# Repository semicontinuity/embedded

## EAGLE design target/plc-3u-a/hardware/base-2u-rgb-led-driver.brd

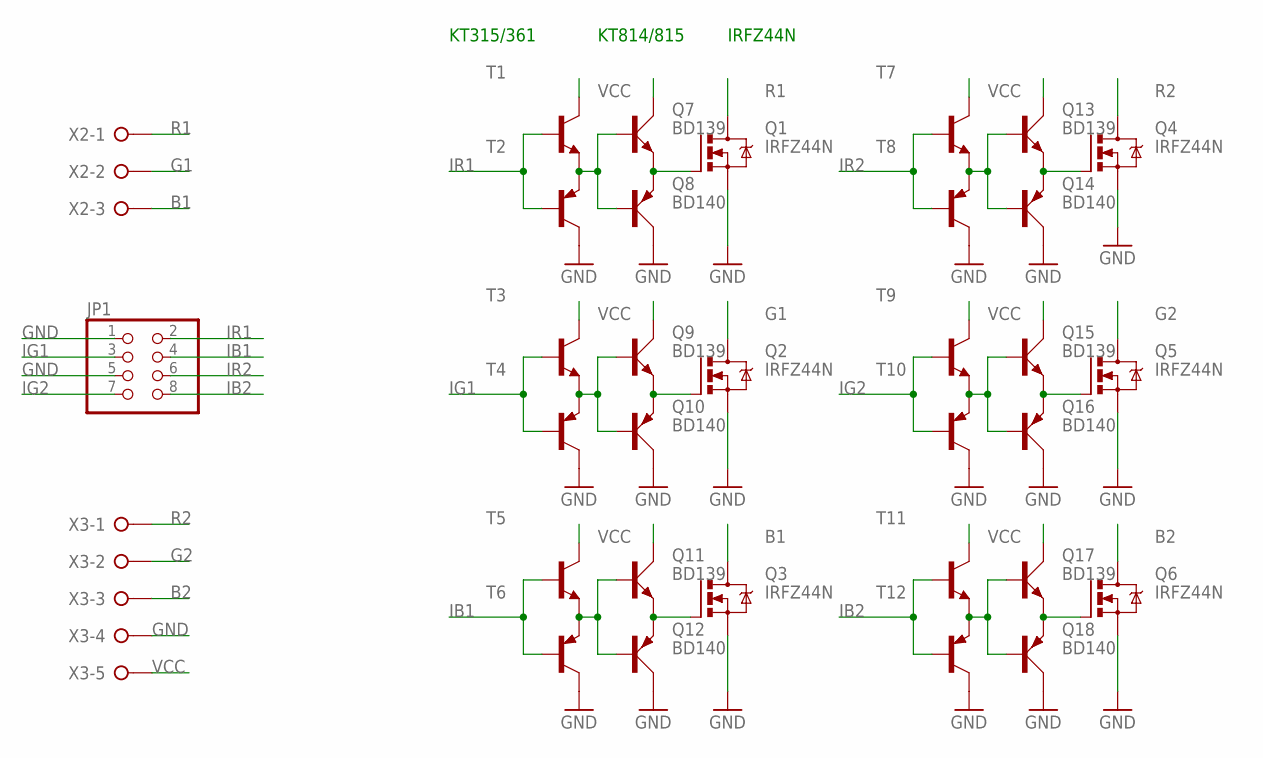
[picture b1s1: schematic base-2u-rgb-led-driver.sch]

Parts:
JP1: PINHD-2X4/90; 2X04/90
Q1, Q2, Q3, Q4, Q5, Q6: IRFZ44N; TO220BV
Q7, Q9, Q11, Q13, Q15, Q17: BD139; TO126AV
Q8, Q10, Q12, Q14, Q16, Q18: BD140; TO126AV
T1, T3, T5, T7, T9, T11: BC637-NPN-TO92-ECB; TO92-ECB
T2, T4, T6, T8, T10, T12: BC638-PNP-TO92-BCE; TO92-BCE
X2: W237-03P; W237-133
X3: W237-05P; W237-5P

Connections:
B1: Q3.D, X2.3
B2: Q6.D, X3.3
DB1: Q11.B, Q12.B, T5.E, T6.E
DB2: Q17.B, Q18.B, T11.E, T12.E
DG1: Q9.B, Q10.B, T3.E, T4.E
DG2: Q15.B, Q16.B, T9.E, T10.E
DR1: Q7.B, Q8.B, T1.E, T2.E
DR2: Q13.B, Q14.B, T7.E, T8.E
G1: Q2.D, X2.2
G2: Q5.D, X3.2
GND: JP1.1, JP1.5, Q1.S, Q2.S, Q3.S, Q4.S, Q5.S, Q6.S, Q8.C, Q10.C, Q12.C, Q14.C, Q16.C, Q18.C, T2.C, T4.C, T6.C, T8.C, T10.C, T12.C, X3.4
IB1: JP1.4, T5.B, T6.B
IB2: JP1.8, T11.B, T12.B
IG1: JP1.3, T3.B, T4.B
IG2: JP1.7, T9.B, T10.B
IR1: JP1.2, T1.B, T2.B
IR2: JP1.6, T7.B, T8.B
unnamed: Q1.G, Q7.E, Q8.E
unnamed: Q4.G, Q13.E, Q14.E
unnamed: Q2.G, Q9.E, Q10.E
unnamed: Q3.G, Q11.E, Q12.E
unnamed: Q5.G, Q15.E, Q16.E
unnamed: Q6.G, Q17.E, Q18.E
R1: Q1.D, X2.1
R2: Q4.D, X3.1
VCC: Q7.C, Q9.C, Q11.C, Q13.C, Q15.C, Q17.C, T1.C, T3.C, T5.C, T7.C, T9.C, T11.C, X3.5

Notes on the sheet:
IRFZ44N
KT315/361
KT814/815

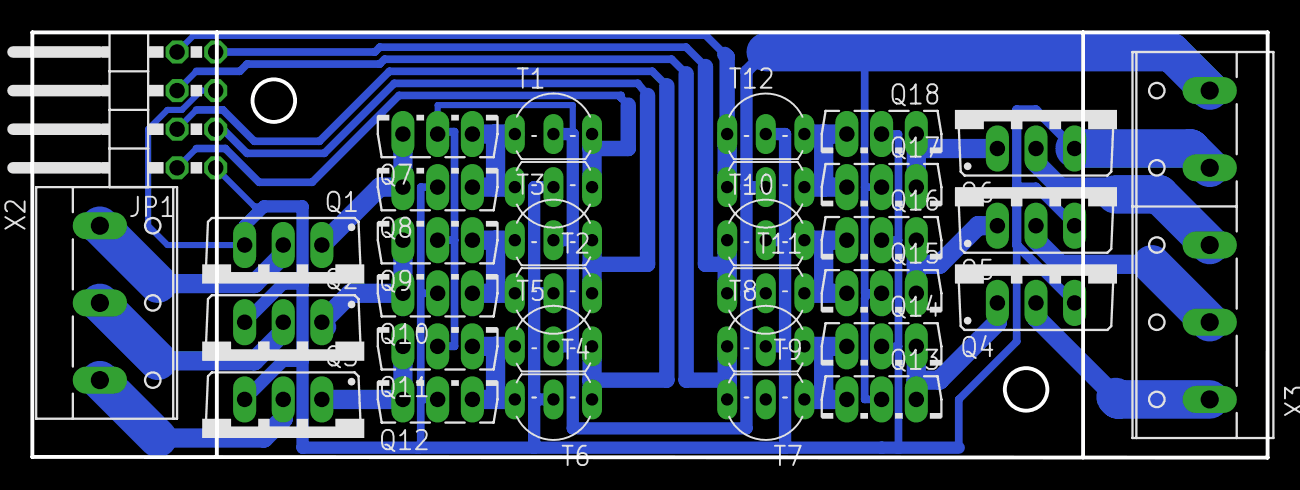
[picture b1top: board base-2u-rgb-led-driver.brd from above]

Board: 2 copper layers, 81.3 x 28.0 mm, 33 parts (0 on the bottom side), 26 nets.

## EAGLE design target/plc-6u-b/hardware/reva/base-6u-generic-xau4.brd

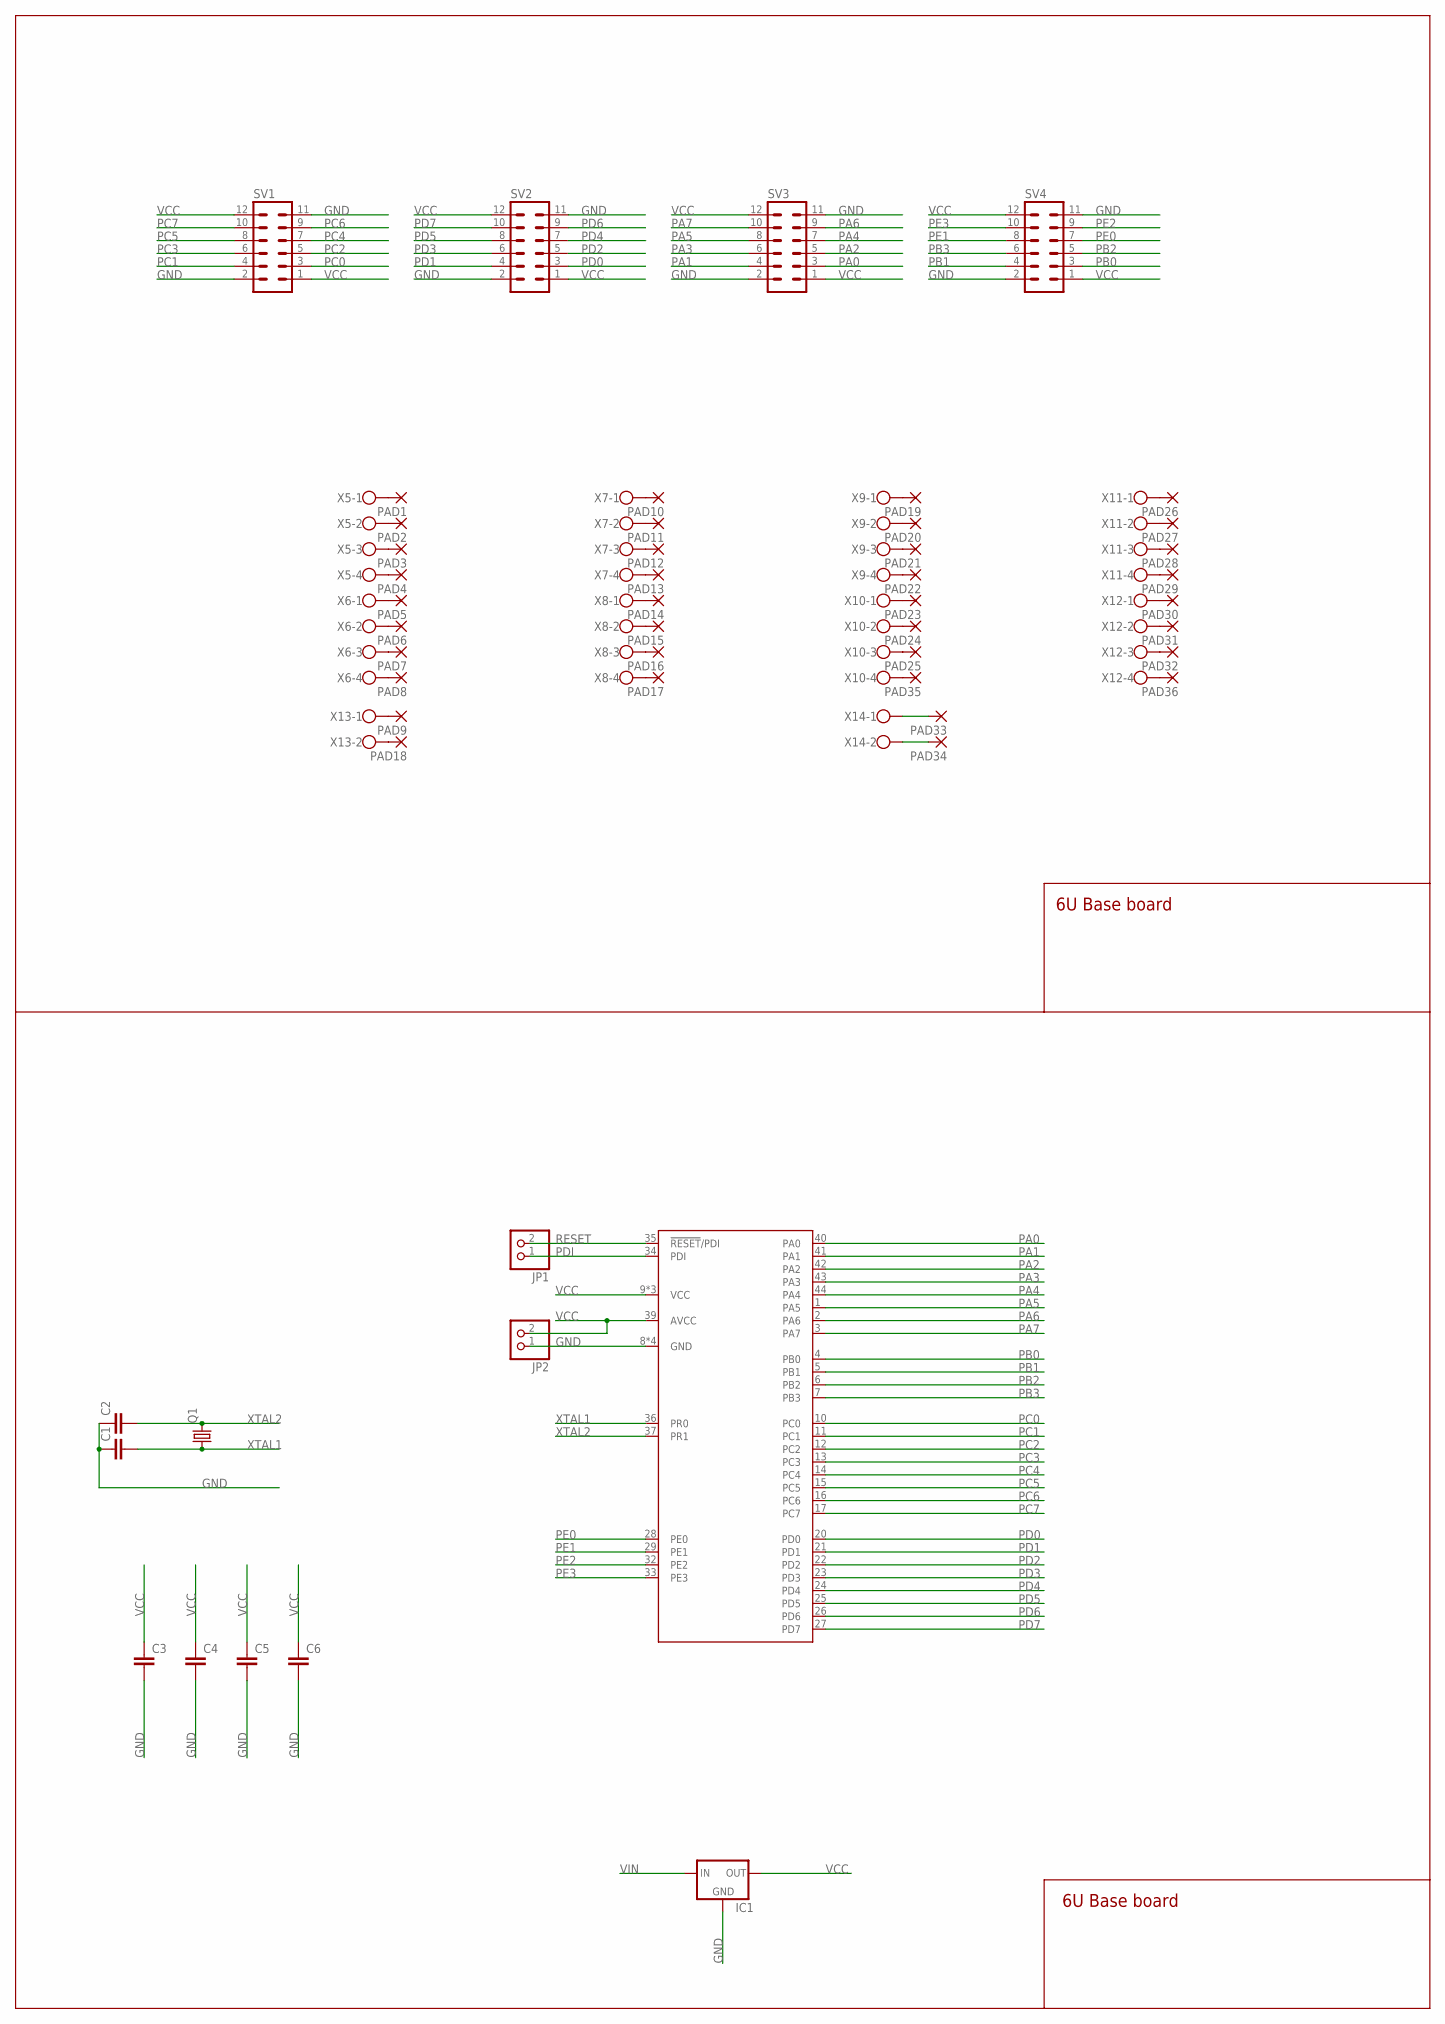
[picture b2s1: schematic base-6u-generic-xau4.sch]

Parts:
C1, C2: C-EUC0805; C0805
C3, C4, C5, C6: C-EUC0603; C0603
IC1: LM1117TO252; TO252
JP1, JP2: PINHD-1X2; 1X02
PAD1, PAD2, PAD3, PAD4, PAD5, PAD6, PAD7, PAD8, PAD9, PAD10, PAD11, PAD12, PAD13, PAD14, PAD15, PAD16, PAD17, PAD18, PAD19, PAD20, PAD21, PAD22, PAD23, PAD24, PAD25, PAD26, PAD27, PAD28, PAD29, PAD30, PAD31, PAD32, PAD33, PAD34, PAD35, PAD36: 2,54/0,8
Q1: CRYSTALHC49S; HC49/S
SV1, SV2, SV3, SV4: MA06-2
U1: ATXMEGA32A4U-AU; TQFP-44A-44
X5, X6, X7, X8, X9, X10, X11, X12: W237-4
X13, X14: W237-102

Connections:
GND: C1.1, C2.1, C3.2, C4.2, C5.2, C6.2, IC1.1 (GND), JP2.1, PAD33.1, SV1.2, SV1.11, SV2.2, SV2.11, SV3.2, SV3.11, SV4.2, SV4.11, U1.8 (GND), U1.18 (GND), U1.30 (GND), U1.38 (GND), X14.1
unnamed: PAD1.1, X5.1
unnamed: PAD2.1, X5.2
unnamed: PAD3.1, X5.3
unnamed: PAD4.1, X5.4
unnamed: PAD5.1, X6.1
unnamed: PAD6.1, X6.2
unnamed: PAD7.1, X6.3
unnamed: PAD8.1, X6.4
unnamed: PAD9.1, X13.1
unnamed: PAD10.1, X7.1
unnamed: PAD11.1, X7.2
unnamed: PAD12.1, X7.3
unnamed: PAD13.1, X7.4
unnamed: PAD14.1, X8.1
unnamed: PAD15.1, X8.2
unnamed: PAD16.1, X8.3
unnamed: PAD17.1, X8.4
unnamed: PAD18.1, X13.2
unnamed: PAD26.1, X11.1
unnamed: PAD27.1, X11.2
unnamed: PAD28.1, X11.3
unnamed: PAD29.1, X11.4
unnamed: PAD30.1, X12.1
unnamed: PAD31.1, X12.2
unnamed: PAD32.1, X12.3
unnamed: PAD19.1, X9.1
unnamed: PAD20.1, X9.2
unnamed: PAD21.1, X9.3
unnamed: PAD22.1, X9.4
unnamed: PAD23.1, X10.1
unnamed: PAD24.1, X10.2
unnamed: PAD25.1, X10.3
unnamed: PAD35.1, X10.4
unnamed: PAD36.1, X12.4
PA0: SV3.3, U1.40 (PA0)
PA1: SV3.4, U1.41 (PA1)
PA2: SV3.5, U1.42 (PA2)
PA3: SV3.6, U1.43 (PA3)
PA4: SV3.7, U1.44 (PA4)
PA5: SV3.8, U1.1 (PA5)
PA6: SV3.9, U1.2 (PA6)
PA7: SV3.10, U1.3 (PA7)
PB0: SV4.3, U1.4 (PB0)
PB1: SV4.4, U1.5 (PB1)
PB2: SV4.5, U1.6 (PB2)
PB3: SV4.6, U1.7 (PB3)
PC0: SV1.3, U1.10 (PC0)
PC1: SV1.4, U1.11 (PC1)
PC2: SV1.5, U1.12 (PC2)
PC3: SV1.6, U1.13 (PC3)
PC4: SV1.7, U1.14 (PC4)
PC5: SV1.8, U1.15 (PC5)
PC6: SV1.9, U1.16 (PC6)
PC7: SV1.10, U1.17 (PC7)
PD0: SV2.3, U1.20 (PD0)
PD1: SV2.4, U1.21 (PD1)
PD2: SV2.5, U1.22 (PD2)
PD3: SV2.6, U1.23 (PD3)
PD4: SV2.7, U1.24 (PD4)
PD5: SV2.8, U1.25 (PD5)
PD6: SV2.9, U1.26 (PD6)
PD7: SV2.10, U1.27 (PD7)
PDI: JP1.1, U1.34 (PDI)
PE0: SV4.7, U1.28 (PE0)
PE1: SV4.8, U1.29 (PE1)
PE2: SV4.9, U1.32 (PE2)
PE3: SV4.10, U1.33 (PE3)
RESET: JP1.2, U1.35 (!RESET!/PDI)
VCC: C3.1, C4.1, C5.1, C6.1, IC1.3 (OUT), JP2.2, SV1.1, SV1.12, SV2.1, SV2.12, SV3.1, SV3.12, SV4.1, SV4.12, U1.9 (VCC), U1.19 (VCC), U1.31 (VCC), U1.39 (AVCC)
VIN: IC1.2 (IN), PAD34.1, X14.2
XTAL1: C1.2, Q1.1, U1.36 (PR0)
XTAL2: C2.2, Q1.2, U1.37 (PR1)

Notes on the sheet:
6U Base board

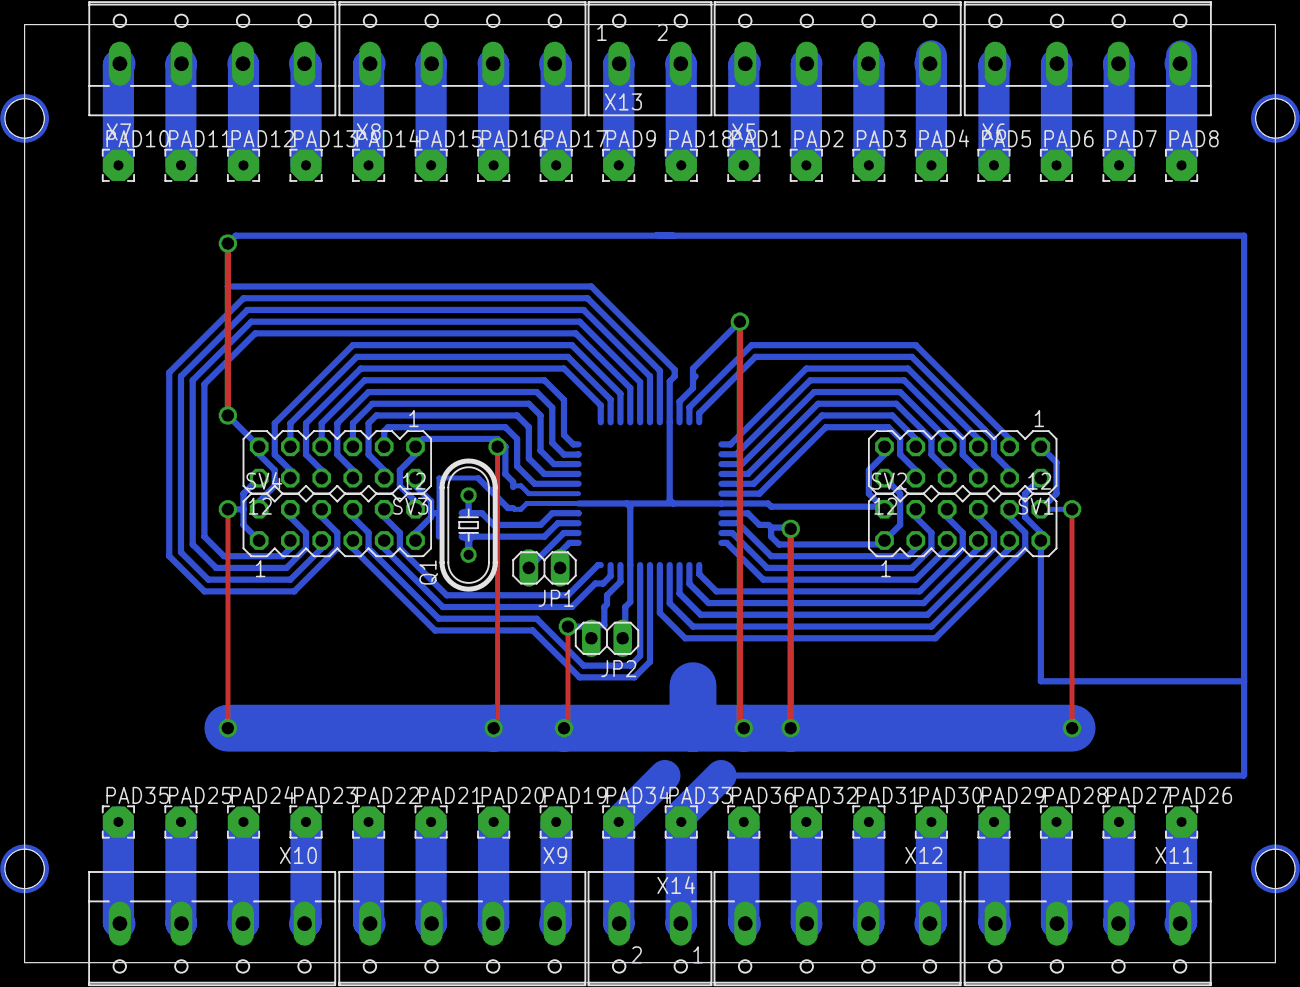
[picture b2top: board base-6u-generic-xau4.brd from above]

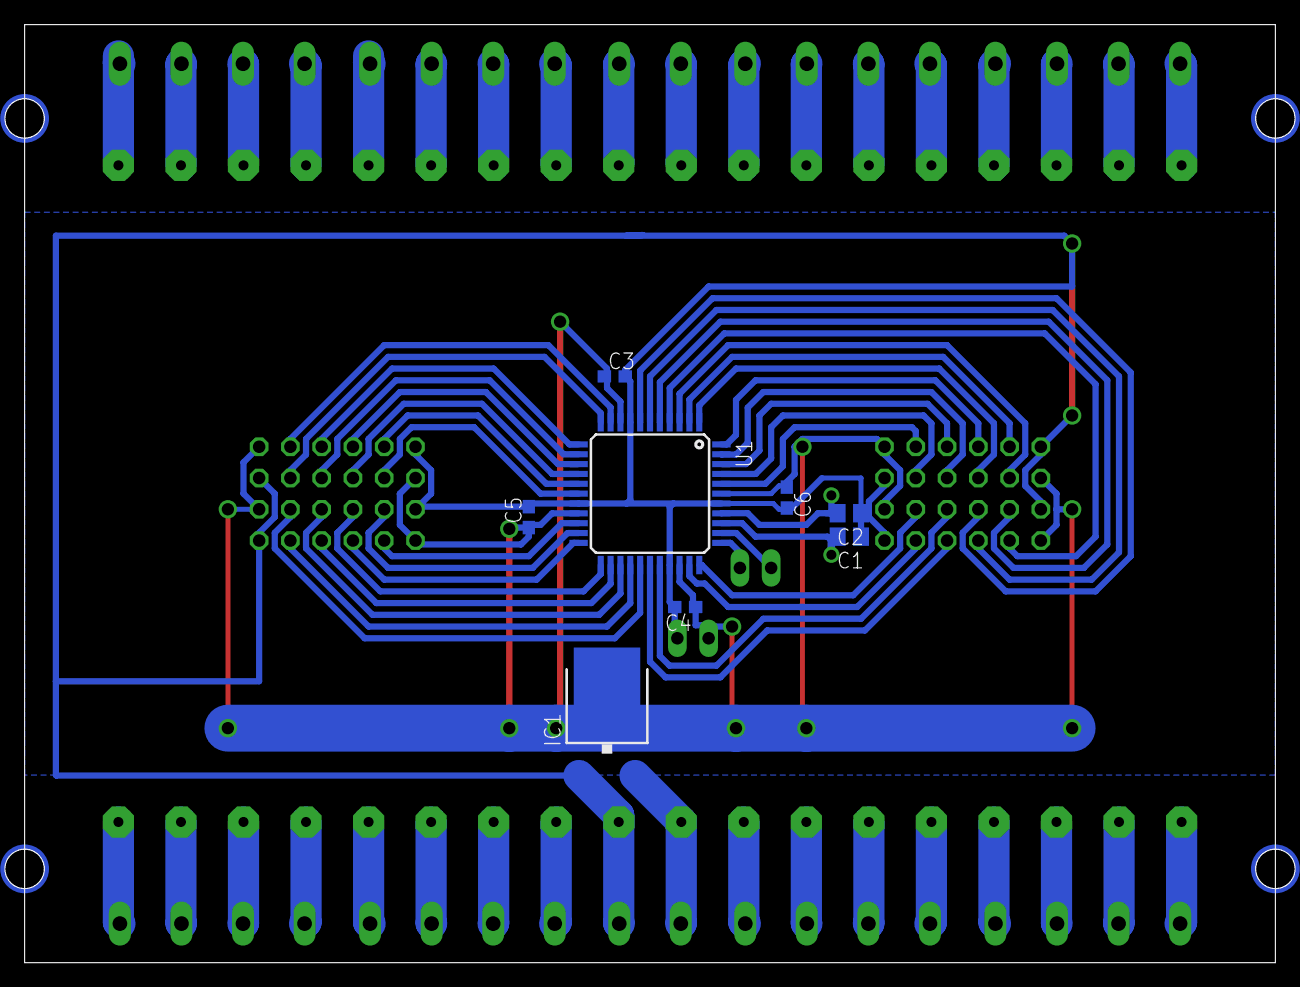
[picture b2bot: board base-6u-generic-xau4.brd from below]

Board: 2 copper layers, 101.6 x 76.2 mm, 61 parts (8 on the bottom side), 73 nets.
